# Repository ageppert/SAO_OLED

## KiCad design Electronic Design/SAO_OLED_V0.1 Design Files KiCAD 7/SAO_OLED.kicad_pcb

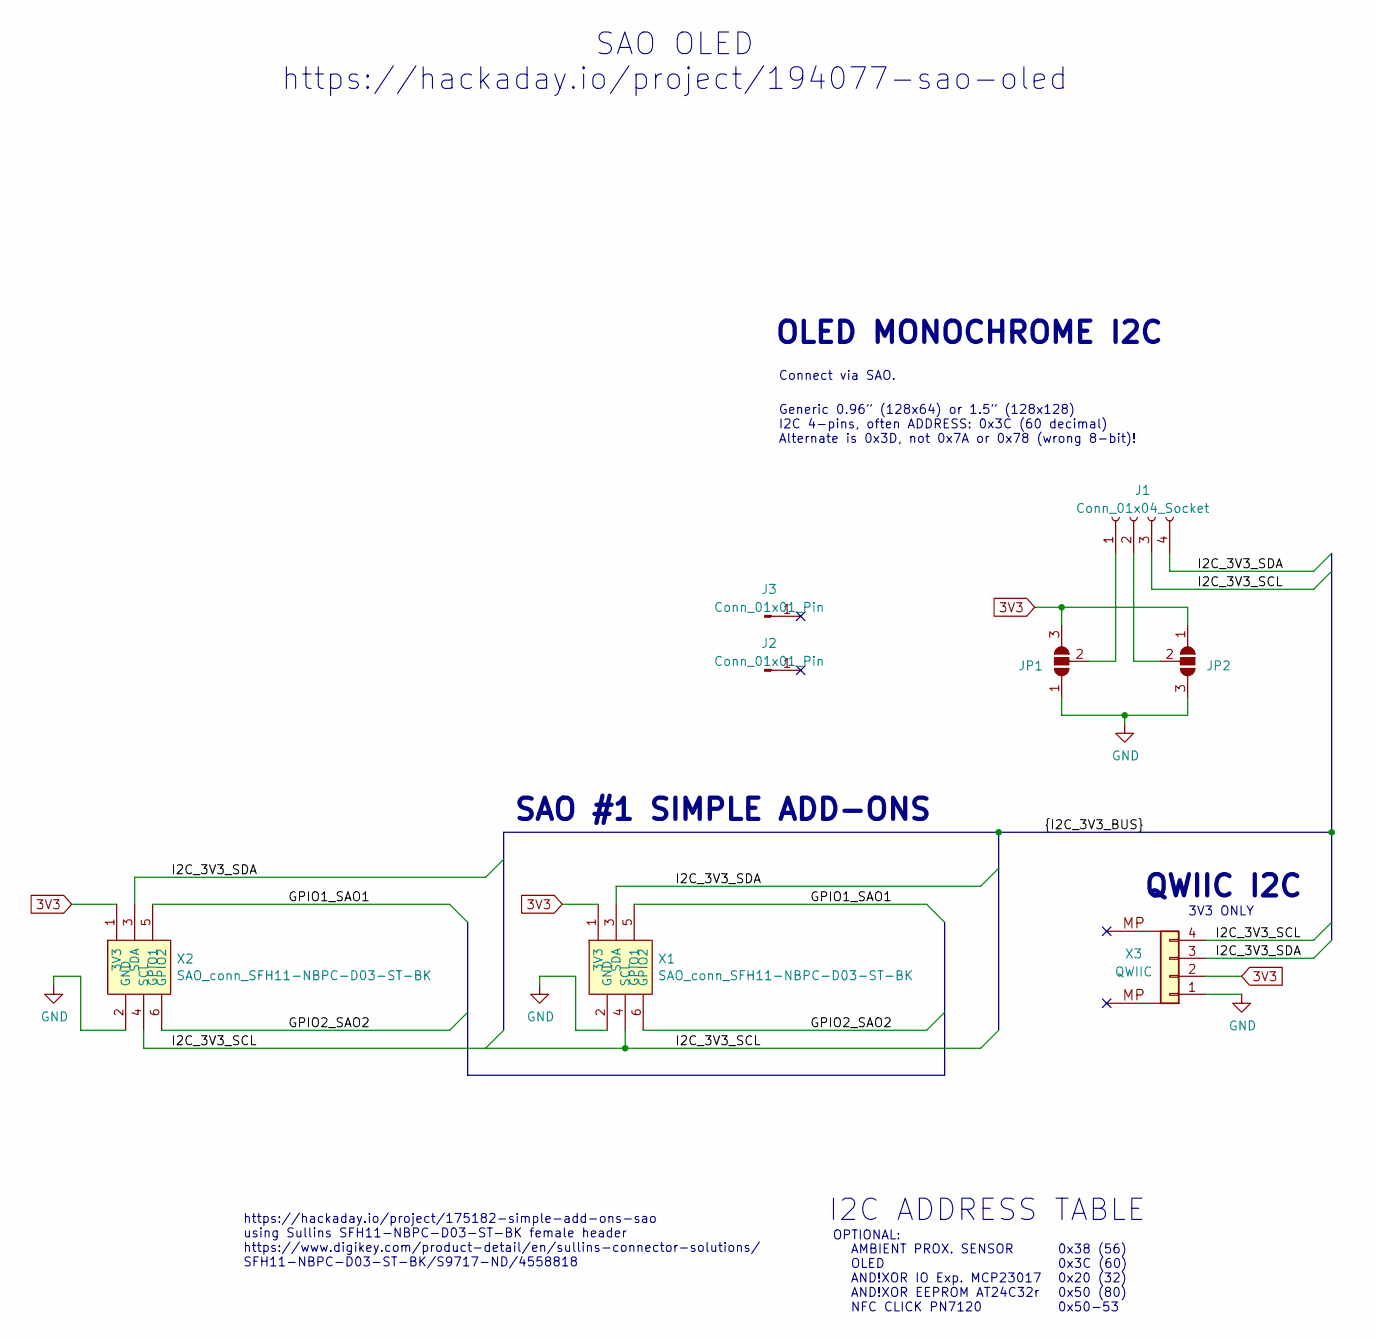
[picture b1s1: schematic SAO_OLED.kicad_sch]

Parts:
J1: Conn_01x04_Socket; PinHeader_1x04_P2.54mm_Vertical
J2, J3: Conn_01x01_Pin; PinHeader_1x01_P2.54mm_Vertical
JP1, JP2: SolderJumper_3_Open-Jumper; SolderJumper-3_P1.3mm_Open_Pad1.0x1.5mm_NumberLabels
X1, X2: SAO_conn_SFH11-NBPC-D03-ST-BK; Badgelife-SAOv169-BADGE-2x3; MPN SFH11-NBPC-D03-ST-BK
X3: QWIIC; JST_SH_SM04B-SRSS-TB_1x04-1MP_P1.00mm_Horizontal; MPN SM04B-SRSS-TB; LCSC C160404

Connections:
3V3: JP1.3 (B), JP2.1 (A), X1.1 (3V3), X2.1 (3V3), X3.2
/GPIO1_SAO1: X1.5 (GPIO1), X2.5 (GPIO1)
/GPIO2_SAO2: X1.6 (GPIO2), X2.6 (GPIO2)
/I2C_3V3_SCL: J1.3, X1.4 (SCL), X2.4 (SCL), X3.4
/I2C_3V3_SDA: J1.4, X1.3 (SDA), X2.3 (SDA), X3.3
GND: JP1.1 (A), JP2.3 (B), X1.2 (GND), X2.2 (GND), X3.1
unnamed: J1.1, JP1.2 (C)
unnamed: J1.2, JP2.2 (C)

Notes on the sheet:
AMBIENT PROX. SENSOR OLED AND!XOR IO Exp. MCP23017 AND!XOR EEPROM AT24C32r NFC CLICK PN7120
https://hackaday.io/project/175182-simple-add-ons-sao using Sullins SFH11-NBPC-D03-ST-BK female header https://www.digikey.com/product-detail/en/sullins-connector-solutions/ SFH11-NBPC-D03-ST-BK/S9717-ND/4558818
SAO #1 SIMPLE ADD-ONS
Generic 0.96” (128x64) or 1.5” (128x128) I2C 4-pins, often ADDRESS: 0x3C (60 decimal) Alternate is 0x3D, not 0x7A or 0x78 (wrong 8-bit)!
SAO OLED https://hackaday.io/project/194077-sao-oled
Connect via SAO.
I2C ADDRESS TABLE
3V3 ONLY
0x38 (56) 0x3C (60) 0x20 (32) 0x50 (80) 0x50-53
QWIIC I2C
OPTIONAL:
OLED MONOCHROME I2C

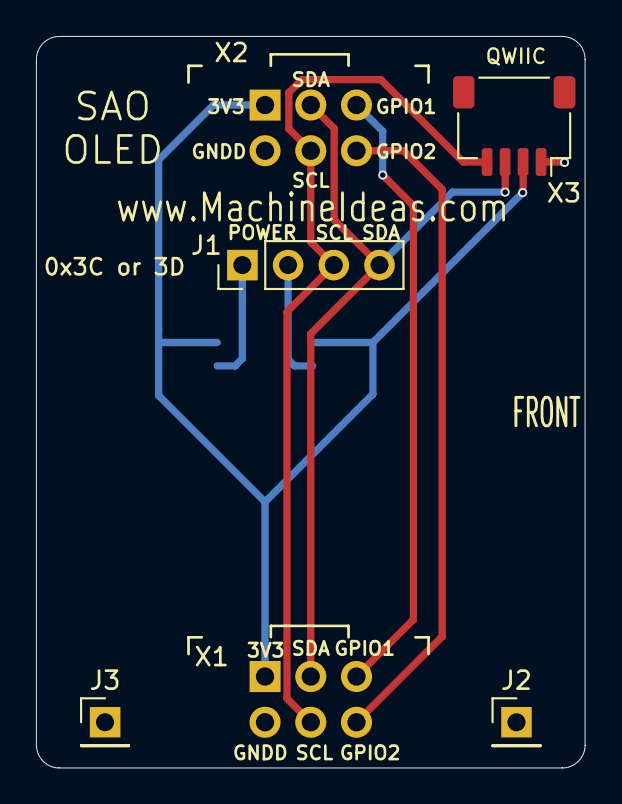
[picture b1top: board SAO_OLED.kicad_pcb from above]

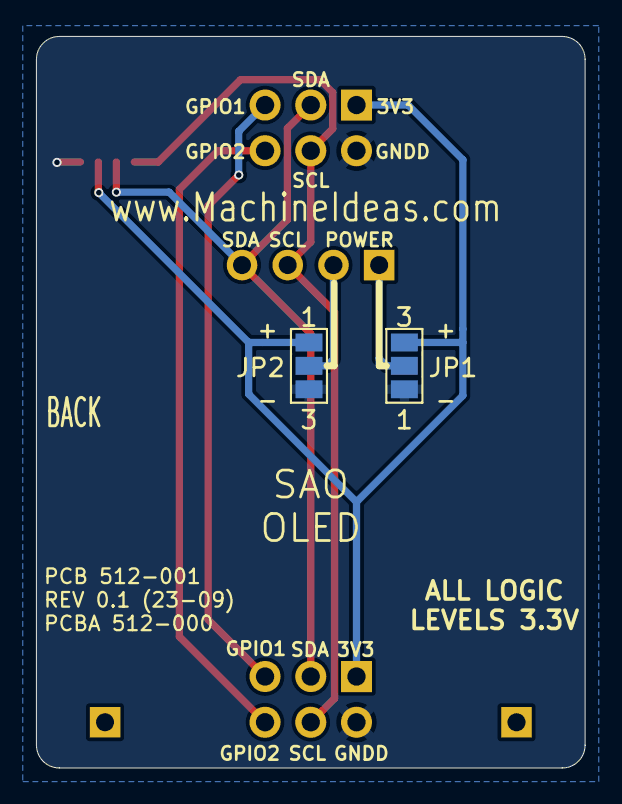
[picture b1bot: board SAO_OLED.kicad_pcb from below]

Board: 2 copper layers, 30.5 x 40.6 mm, 8 parts (2 on the bottom side), 8 nets.

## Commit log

2024-05-01 V0.1 Initial commit.
